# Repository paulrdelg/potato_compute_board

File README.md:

# Potato Compute Board

## Description

Potato compute is simple PCB microcrontroller with USB-C connector designed with KiCad.

## KiCad

Used version 8.0.7

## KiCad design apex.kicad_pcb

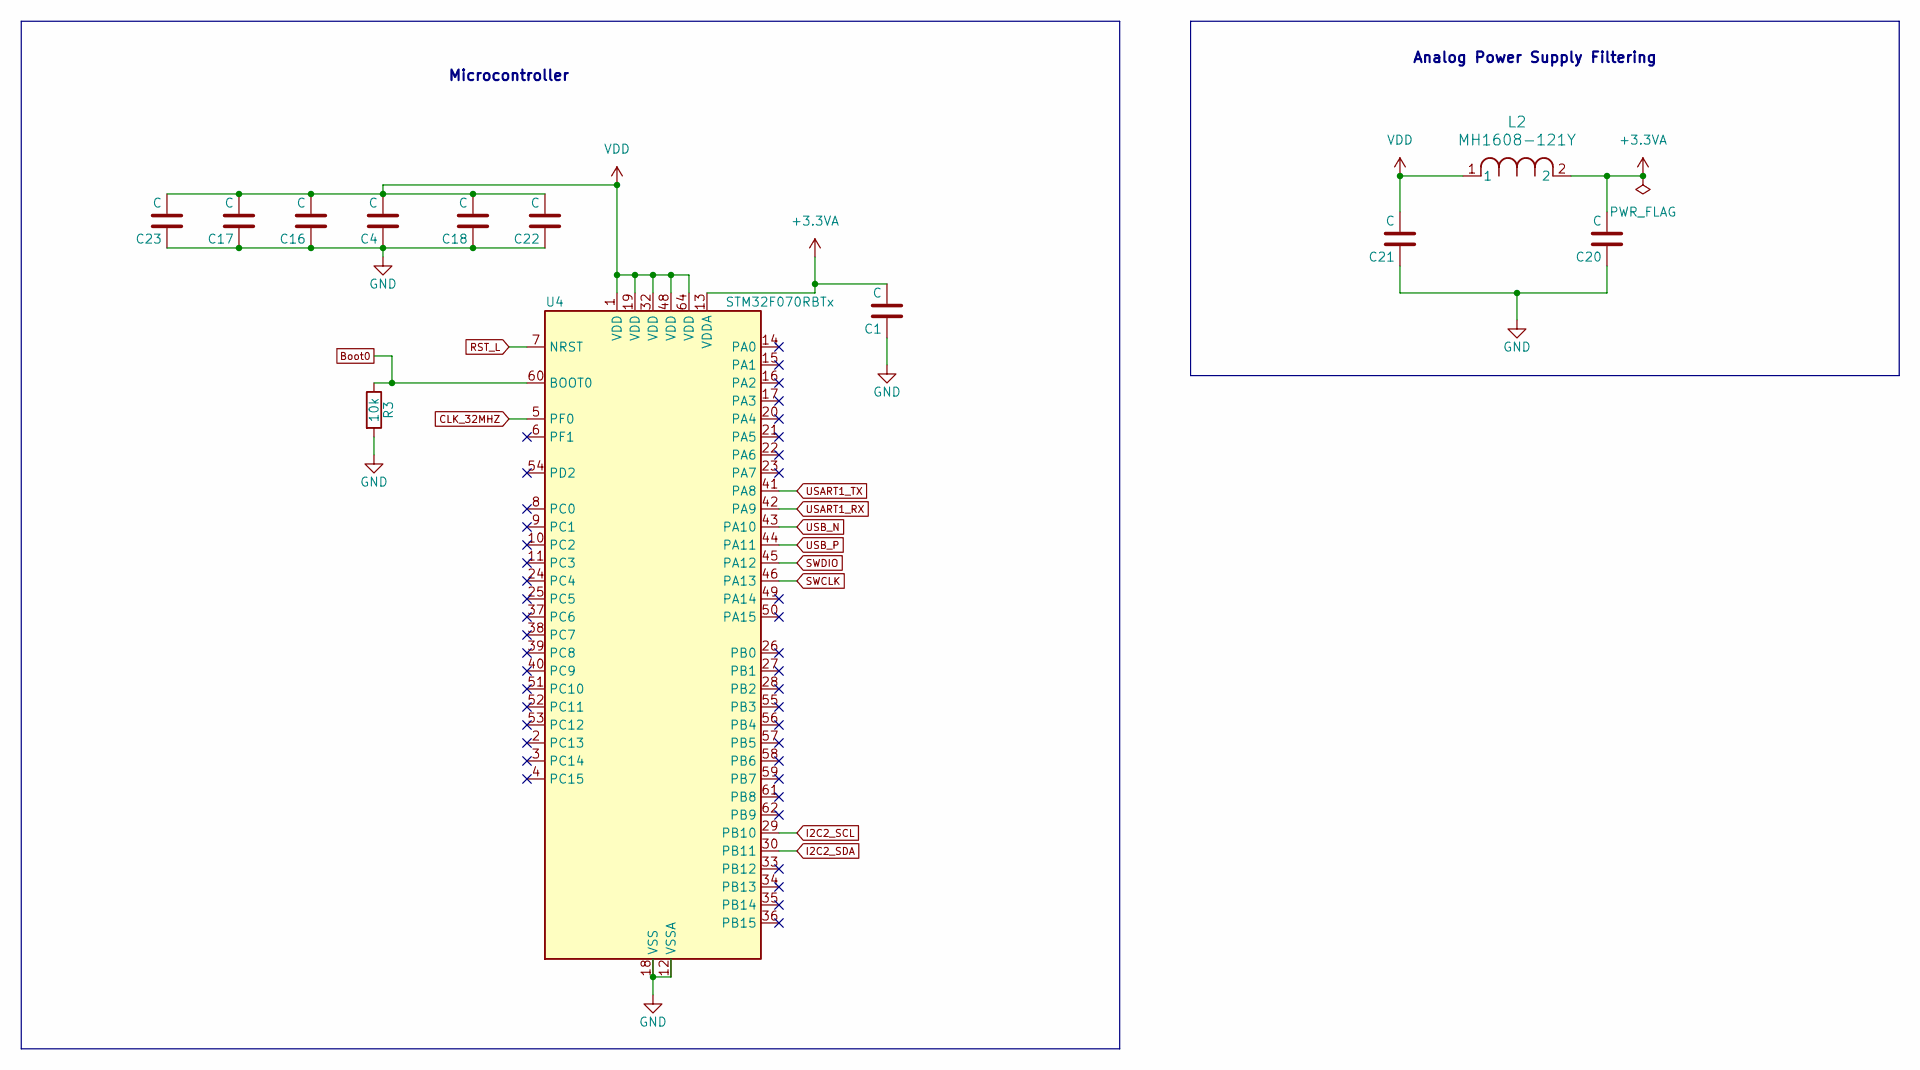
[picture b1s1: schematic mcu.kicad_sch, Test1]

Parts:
C1, C4, C16, C17, C18, C20, C21, C22, C23: C; C_0805_2012Metric
L2: MH1608-121Y; IND_BOURNS_MH1608
R3: 10k; R_0805_2012Metric
U4: STM32F070RBTx; LQFP-64_10x10mm_P0.5mm

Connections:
+3.3VA: C1.2, C20.2, L2.2, U4.13 (VDDA)
Boot0: R3.1, U4.60 (BOOT0)
CLK_32MHZ: U4.5 (PF0); also elsewhere on the board
GND: C1.1, C4.1, C16.1, C17.1, C18.1, C20.1, C21.1, C22.1, C23.1, R3.2, U4.12 (VSSA), U4.18 (VSS), U4.31 (VSS), U4.47 (VSS), U4.63 (VSS); also elsewhere on the board
I2C2_SCL: U4.29 (PB10); also elsewhere on the board
I2C2_SDA: U4.30 (PB11); also elsewhere on the board
RST_L: U4.7 (NRST); also elsewhere on the board
SWCLK: U4.46 (PA13); also elsewhere on the board
SWDIO: U4.45 (PA12); also elsewhere on the board
USART1_RX: U4.42 (PA9); also elsewhere on the board
USART1_TX: U4.41 (PA8); also elsewhere on the board
USB_N: U4.43 (PA10); also elsewhere on the board
USB_P: U4.44 (PA11); also elsewhere on the board
VDD: C4.2, C16.2, C17.2, C18.2, C21.2, C22.2, C23.2, L2.1, U4.1 (VDD), U4.19 (VDD), U4.32 (VDD), U4.48 (VDD), U4.64 (VDD); also elsewhere on the board

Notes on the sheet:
Analog Power Supply Filtering
Microcontroller

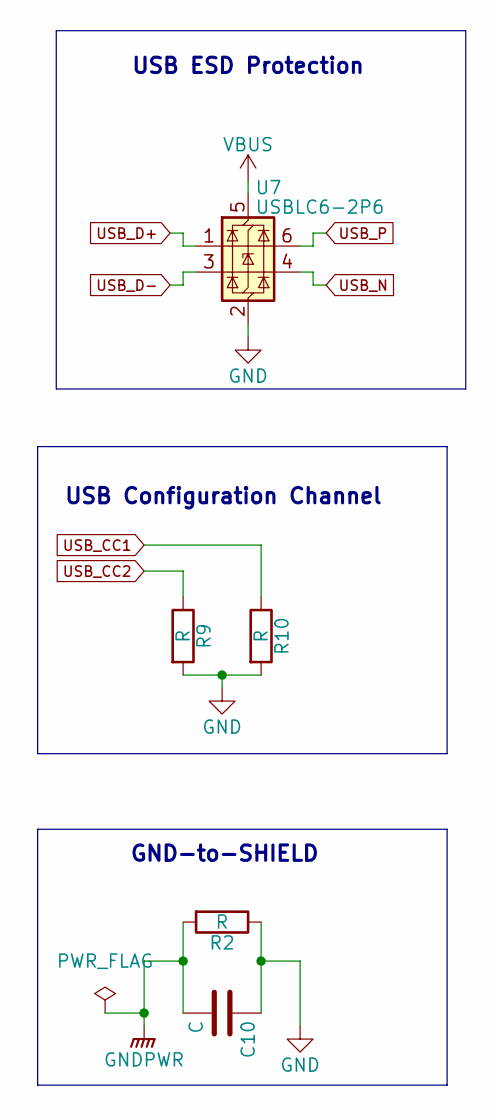
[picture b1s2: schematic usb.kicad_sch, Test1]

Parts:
C10: C; C_0805_2012Metric
R2, R9, R10: R; R_0805_2012Metric
U7: USBLC6-2P6; SOT-666

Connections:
GND: C10.1, R2.1, R9.2, R10.2, U7.2 (GND); also elsewhere on the board
GNDPWR: C10.2, R2.2; also elsewhere on the board
USB_CC1: R10.1; also elsewhere on the board
USB_CC2: R9.1; also elsewhere on the board
USB_D+: U7.1 (I/O1); also elsewhere on the board
USB_D-: U7.3 (I/O2); also elsewhere on the board
USB_N: U7.4 (I/O2); also elsewhere on the board
USB_P: U7.6 (I/O1); also elsewhere on the board
VBUS: U7.5 (VBUS); also elsewhere on the board

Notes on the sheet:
USB ESD Protection
USB Configuration Channel
GND-to-SHIELD

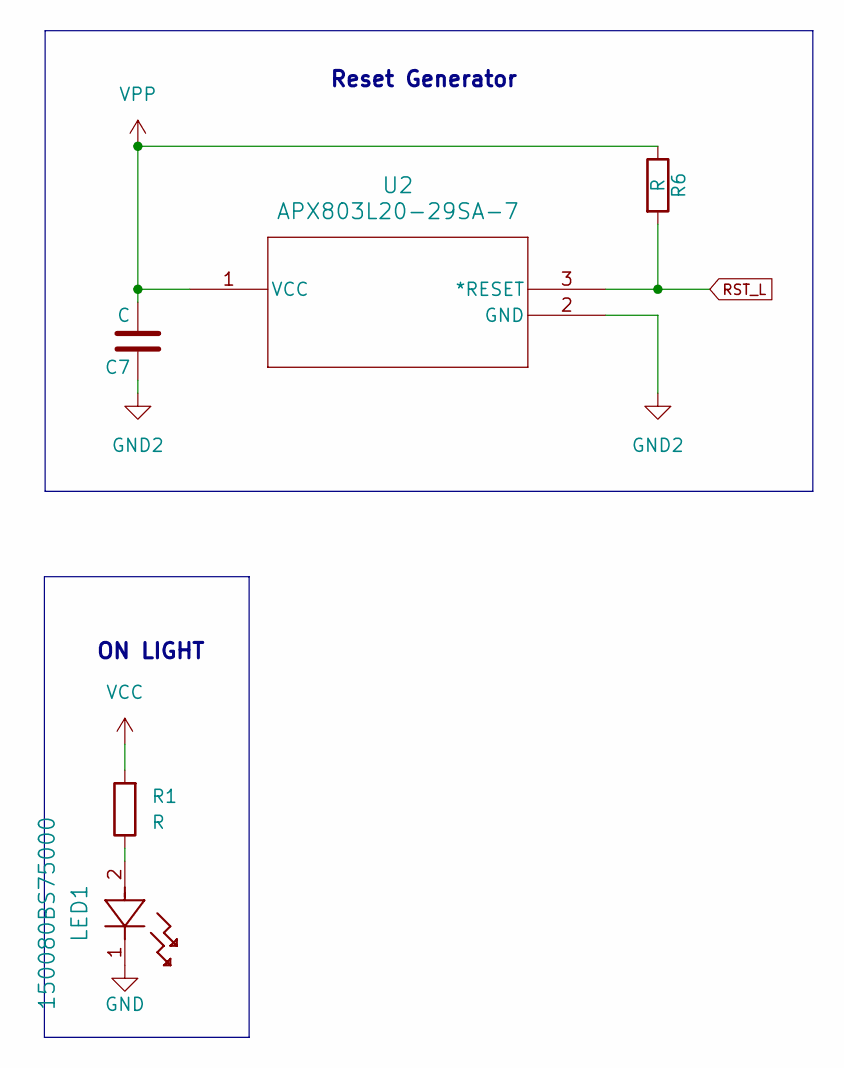
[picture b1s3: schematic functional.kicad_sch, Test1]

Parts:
C7: C; C_0805_2012Metric
LED1: 150080BS75000
R1, R6: R; R_0805_2012Metric
U2: APX803L20-29SA-7; SOT23_SA_DIO

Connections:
GND: C7.1, LED1.1, U2.2 (GND); also elsewhere on the board
unnamed: LED1.2, R1.1
RST_L: R6.2, U2.3 (*RESET); also elsewhere on the board
VCC: R1.2; also elsewhere on the board
VPP: C7.2, R6.1, U2.1 (VCC); also elsewhere on the board

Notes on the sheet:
ON LIGHT
Reset Generator

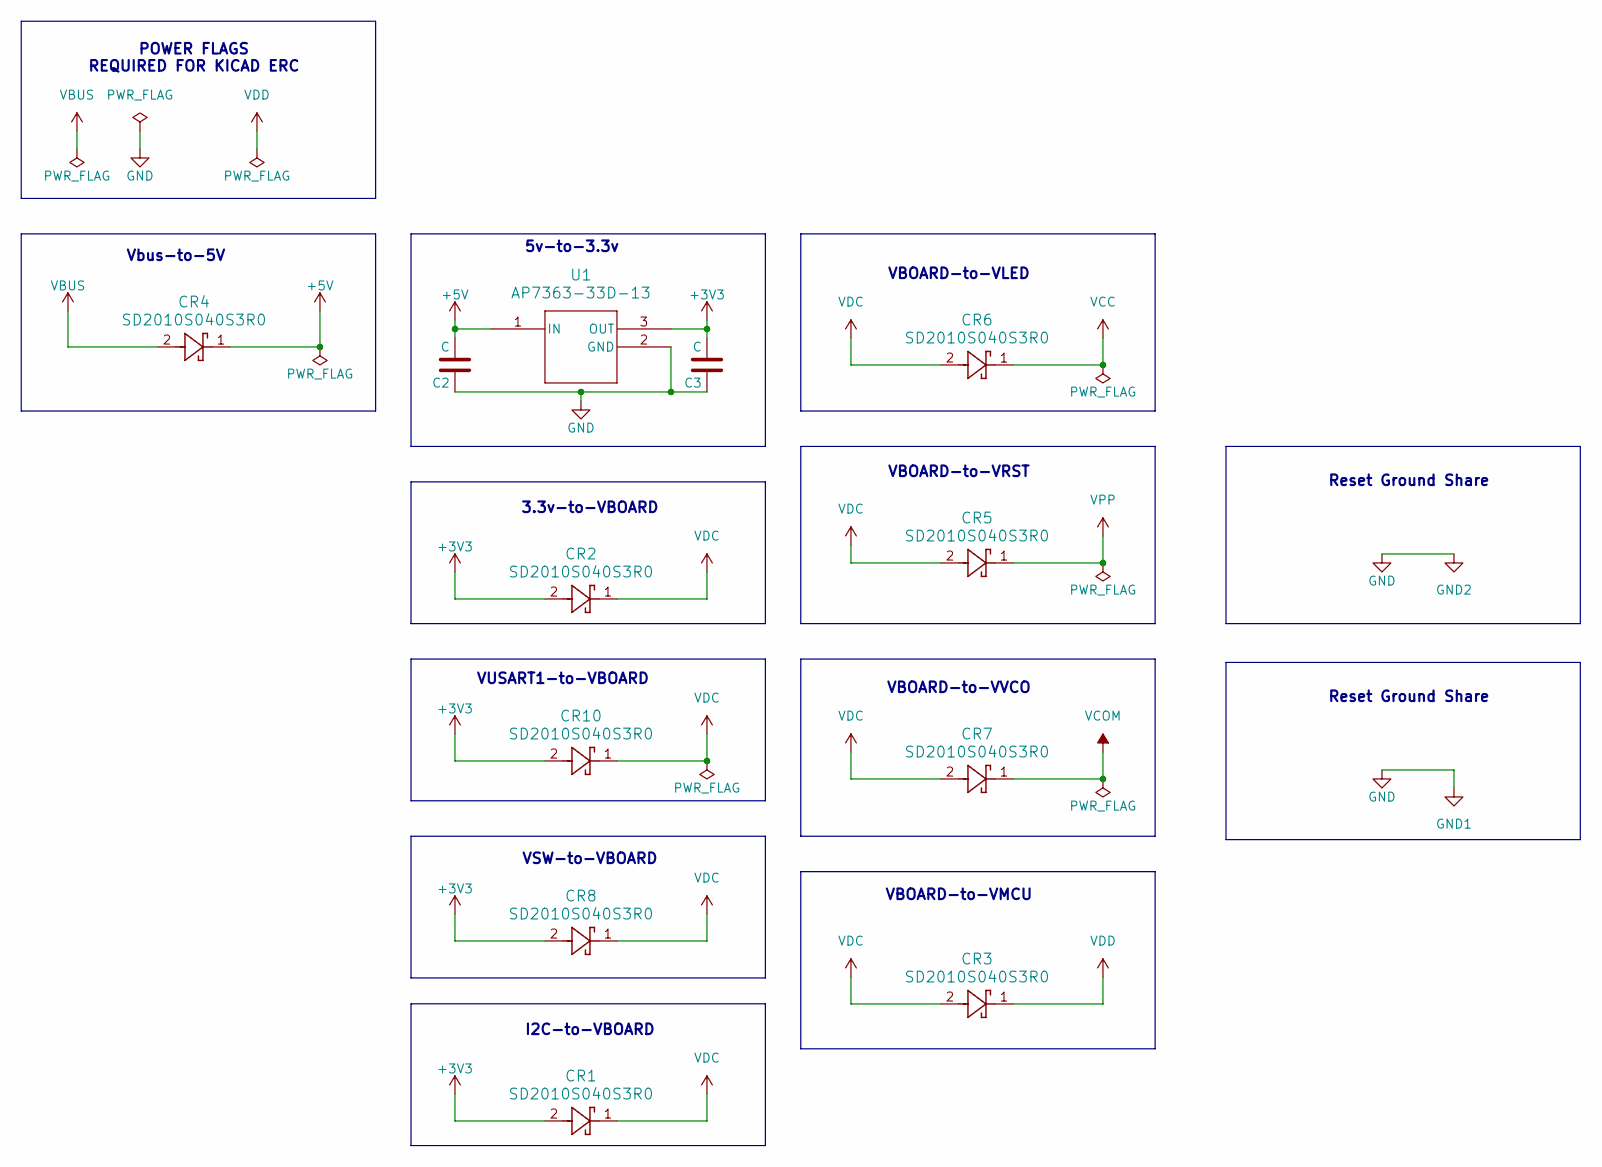
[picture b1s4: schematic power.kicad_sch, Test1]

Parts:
C2, C3: C; C_0805_2012Metric
CR1, CR2, CR3, CR4, CR5, CR6, CR7, CR8, CR10: SD2010S040S3R0; SDO_KAVX_KAV
U1: AP7363-33D-13; TO252-3L_DIO

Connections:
+3V3: C3.2, CR1.2, CR2.2, CR8.2, CR10.2, U1.3 (OUT); also elsewhere on the board
+5V: C2.2, CR4.1, U1.1 (IN)
GND: C2.1, C3.1, U1.2 (GND); also elsewhere on the board
VBUS: CR4.2; also elsewhere on the board
VCC: CR6.1; also elsewhere on the board
VCOM: CR7.1; also elsewhere on the board
VDC: CR1.1, CR2.1, CR3.2, CR5.2, CR6.2, CR7.2, CR8.1, CR10.1
VDD: CR3.1; also elsewhere on the board
VPP: CR5.1; also elsewhere on the board

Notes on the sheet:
Vbus-to-5V
5v-to-3.3v
VUSART1-to-VBOARD
Reset Ground Share
VBOARD-to-VMCU
VBOARD-to-VVCO
VBOARD-to-VLED
VBOARD-to-VRST
I2C-to-VBOARD
POWER FLAGS REQUIRED FOR KICAD ERC
VSW-to-VBOARD
3.3v-to-VBOARD

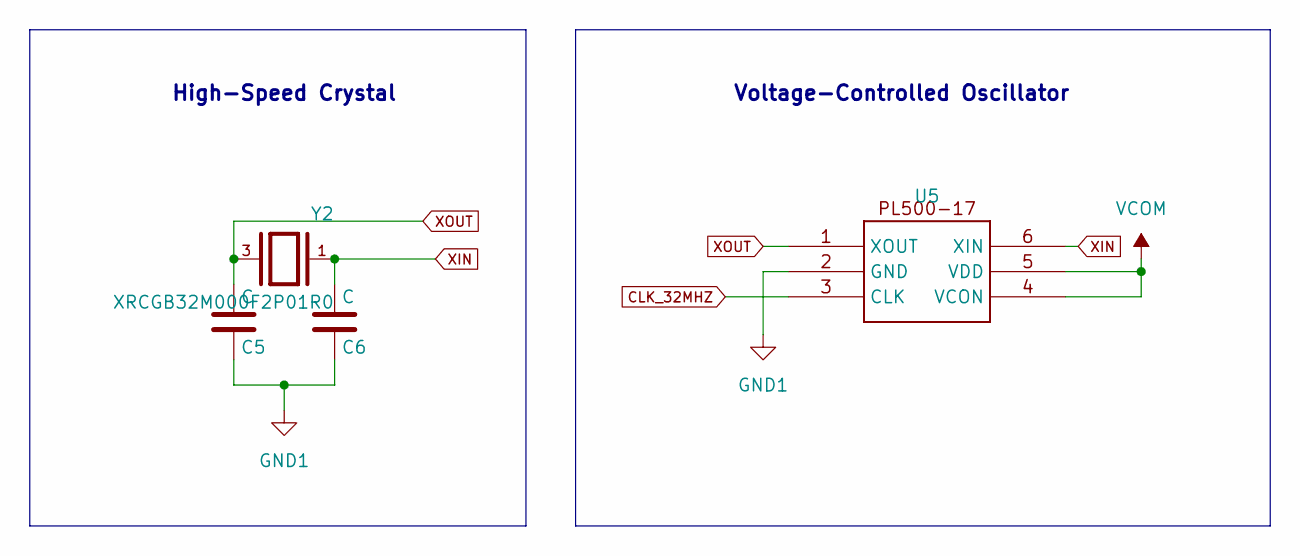
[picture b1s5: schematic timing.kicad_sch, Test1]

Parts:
C5, C6: C; C_0805_2012Metric
U5: SOIC-8-1EP_3.9x4.9mm_P1.27mm_EP2.41x3.3mm
Y2: XRCGB32M000F2P01R0; OSC_XRCGB32M000F2P01R0; PARTREV N/A

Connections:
CLK_32MHZ: U5.3 (CLK); also elsewhere on the board
GND: C5.1, C6.1, U5.2 (GND); also elsewhere on the board
VCOM: U5.4 (VCON), U5.5 (VDD); also elsewhere on the board
XIN: C6.2, U5.6 (XIN), Y2.1
XOUT: C5.2, U5.1 (XOUT), Y2.3

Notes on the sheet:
Voltage-Controlled Oscillator
High-Speed Crystal

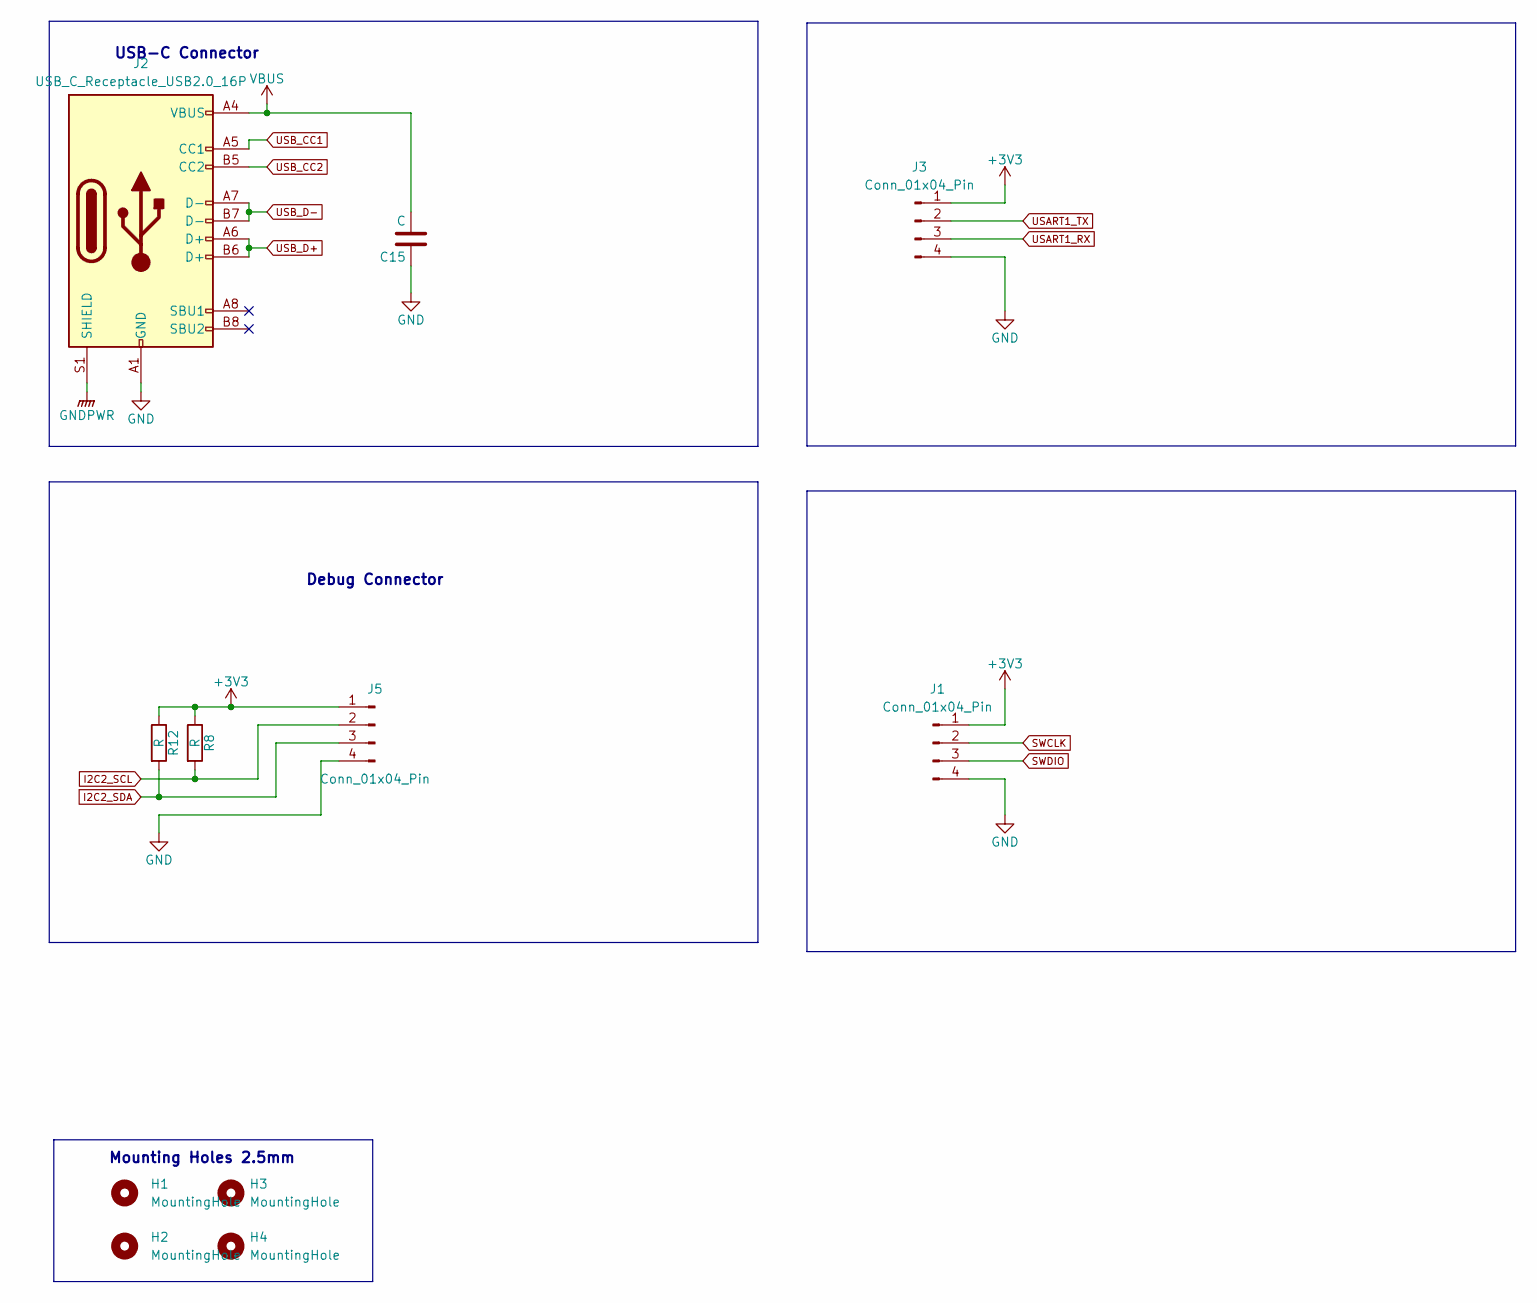
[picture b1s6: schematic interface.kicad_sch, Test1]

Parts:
C15: C; C_0805_2012Metric
H1, H2, H3, H4: MountingHole; MountingHole_2.5mm_Pad
J1, J3, J5: Conn_01x04_Pin; PPTC041LFBN-RC
J2: USB_C_Receptacle_USB2.0_16P; USB_C_Receptacle_GCT_USB4110
R8, R12: R; R_0805_2012Metric

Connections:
+3V3: J1.1, J3.1, J5.1, R8.1, R12.1; also elsewhere on the board
GND: C15.1, J1.4, J2.A1 (GND), J2.A12 (GND), J2.B1 (GND), J2.B12 (GND), J3.4, J5.4; also elsewhere on the board
GNDPWR: J2.S1 (SHIELD); also elsewhere on the board
I2C2_SCL: J5.2, R8.2; also elsewhere on the board
I2C2_SDA: J5.3, R12.2; also elsewhere on the board
SWCLK: J1.2; also elsewhere on the board
SWDIO: J1.3; also elsewhere on the board
USART1_RX: J3.3; also elsewhere on the board
USART1_TX: J3.2; also elsewhere on the board
USB_CC1: J2.A5 (CC1); also elsewhere on the board
USB_CC2: J2.B5 (CC2); also elsewhere on the board
USB_D+: J2.A6 (D+), J2.B6 (D+); also elsewhere on the board
USB_D-: J2.A7 (D-), J2.B7 (D-); also elsewhere on the board
VBUS: C15.2, J2.A4 (VBUS), J2.A9 (VBUS), J2.B4 (VBUS), J2.B9 (VBUS); also elsewhere on the board

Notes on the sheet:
USB-C Connector
Debug Connector
Mounting Holes 2.5mm

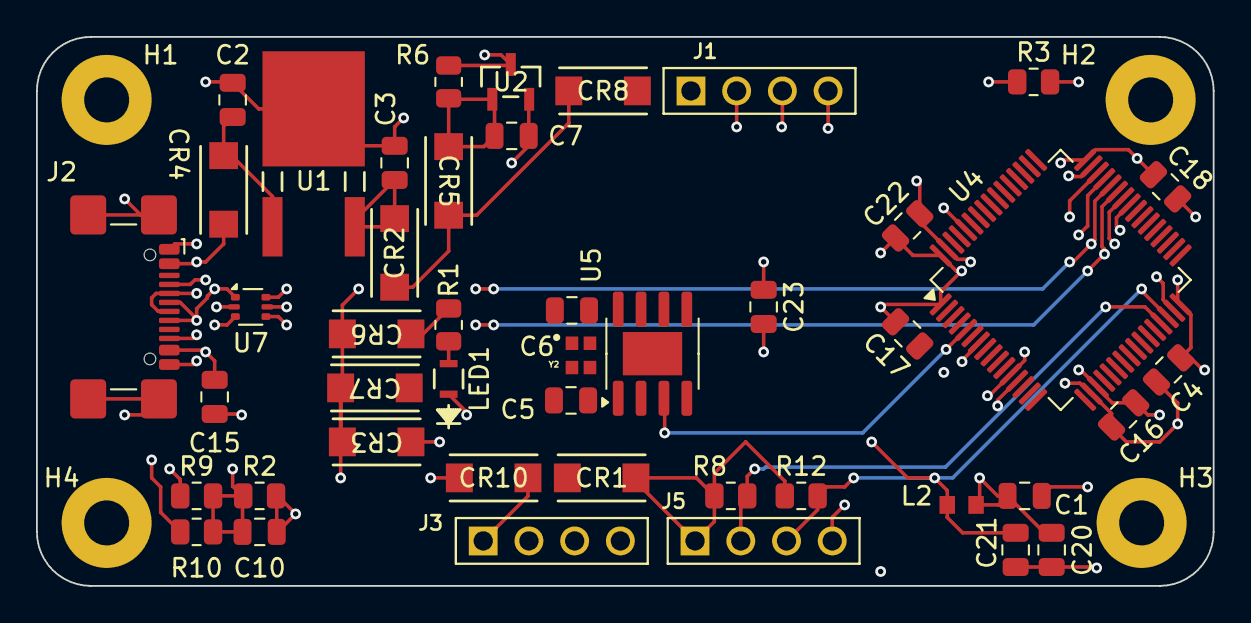
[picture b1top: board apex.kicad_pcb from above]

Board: 4 copper layers, 65.4 x 30.5 mm, 49 parts (0 on the bottom side), 29 nets.

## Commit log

2024-05-25 added models
2024-05-25 added project, schematic, layout
2024-05-25 added README
2024-05-26 re-added symbols
2024-05-27 started footprint
2024-12-15 added split worksheets
2024-12-25 finished ERC, matched footprints, populated 3D models
2024-12-25 added kicad gitignore
2024-12-25 cleaned up model organization
2024-12-25 updated README, removed directories, remapping footprints
2024-12-25 matched footprint name to name of component
2024-12-25 renamed symbols to component name
2024-12-25 renamed symbols
2024-12-25 updated libraries
2024-12-25 updated symbol names
2024-12-25 renamed unused symbols
2024-12-25 removed unused symbols
2024-12-25 removed unused models
2024-12-25 removed manual switch
2024-12-25 removed AVR mcu
2024-12-26 added diode
2024-12-26 separated voltage source labels
2024-12-26 isolated v sources
2024-12-27 updating pcb
2024-12-29 added sheets
